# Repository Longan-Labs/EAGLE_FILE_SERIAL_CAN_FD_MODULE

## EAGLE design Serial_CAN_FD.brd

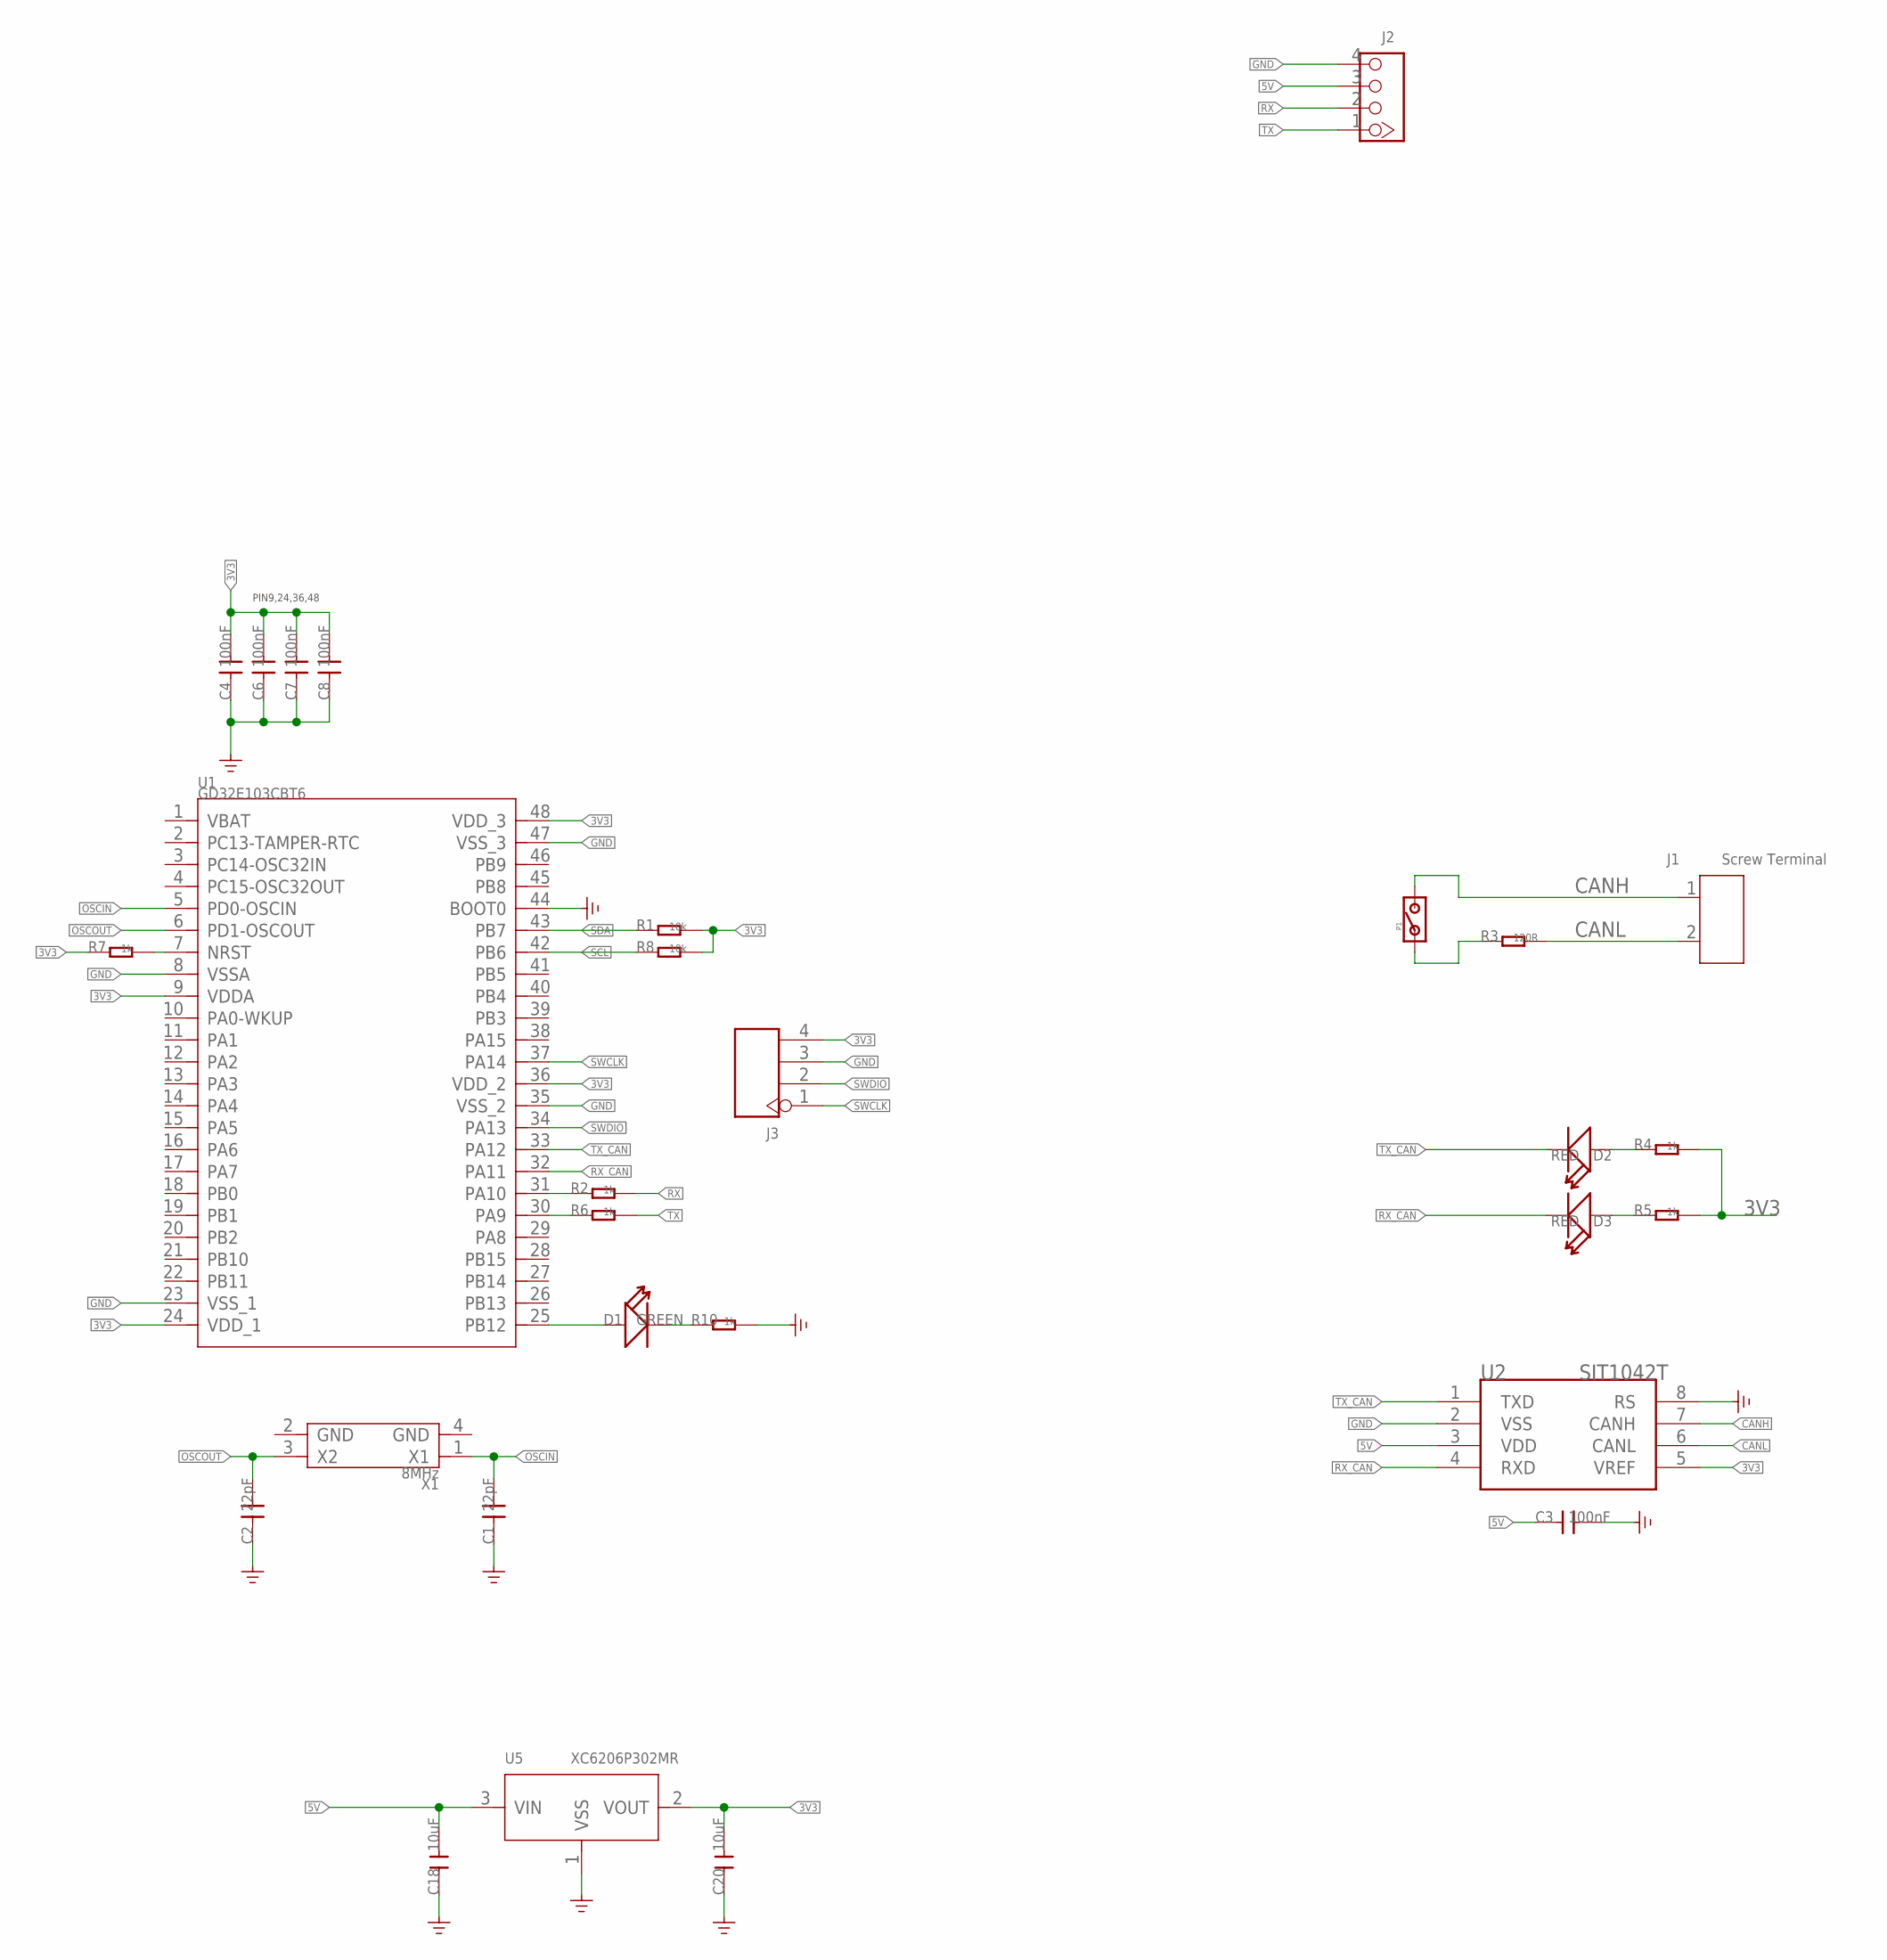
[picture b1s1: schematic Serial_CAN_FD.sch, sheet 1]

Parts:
C1, C2: 22pF; 0603
C3, C4, C6, C7, C8: 100nF; 0603
C18, C20: 10uF; C0603
D1: GREEN; LED-0603
D2, D3: RED; LED-0603
J1: Screw Terminal; 2P-3.5
J2: 320110033; HW4-2.0
J3: HEADER-4P-65/35MIL; H4-2.54
P1: PAD-JUMPER-2P; 2P-SMD-1.78X1.27
R1, R8: 10k; 0603
R2, R4, R5, R6, R7, R10: 1k; 0603
R3: 120R; 0603
U1: GD32E103CBT6; LQFP48
U2: SIT1042T; SOIC8-6.0
U5: XC6206P302MR; SOT-23
X1: 8MHz; X4-SMD-3.2X2.5X0.7MM

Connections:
3V3: C4.2, C6.2, C7.2, C8.2, C20.2, J3.4, R1.2, R4.2, R5.2, R7.1, R8.2, U1.9 (VDDA), U1.24 (VDD_1), U1.36 (VDD_2), U1.48 (VDD_3), U2.5 (VREF), U5.2 (VOUT)
5V: C3.1, C18.2, J2.3, U2.3 (VDD), U5.3 (VIN)
CANH: J1.1, P1.2, U2.7 (CANH)
CANL: J1.2, R3.2, U2.6 (CANL)
GND: C1.1, C2.1, C3.2, C4.1, C6.1, C7.1, C8.1, C18.1, C20.1, J2.4, J3.3, R10.2, U1.8 (VSSA), U1.23 (VSS_1), U1.35 (VSS_2), U1.44 (BOOT0), U1.47 (VSS_3), U2.2 (VSS), U2.8 (RS), U5.1 (VSS)
unnamed: P1.1, R3.1
unnamed: D2.+, R4.1
unnamed: R2.1, U1.31 (PA10)
unnamed: R6.1, U1.30 (PA9)
unnamed: D1.+, U1.25 (PB12)
unnamed: R7.2, U1.7 (NRST)
unnamed: D1.-, R10.1
unnamed: D3.+, R5.1
OSCIN: C1.2, U1.5 (PD0-OSCIN), X1.1 (X1)
OSCOUT: C2.2, U1.6 (PD1-OSCOUT), X1.3 (X2)
RX: J2.2, R2.2
RX_CAN: D3.-, U1.32 (PA11), U2.4 (RXD)
SCL: R8.1, U1.42 (PB6)
SDA: R1.1, U1.43 (PB7)
SWCLK: J3.1, U1.37 (PA14)
SWDIO: J3.2, U1.34 (PA13)
TX: J2.1, R6.2
TX_CAN: D2.-, U1.33 (PA12), U2.1 (TXD)

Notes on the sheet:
PIN9,24,36,48

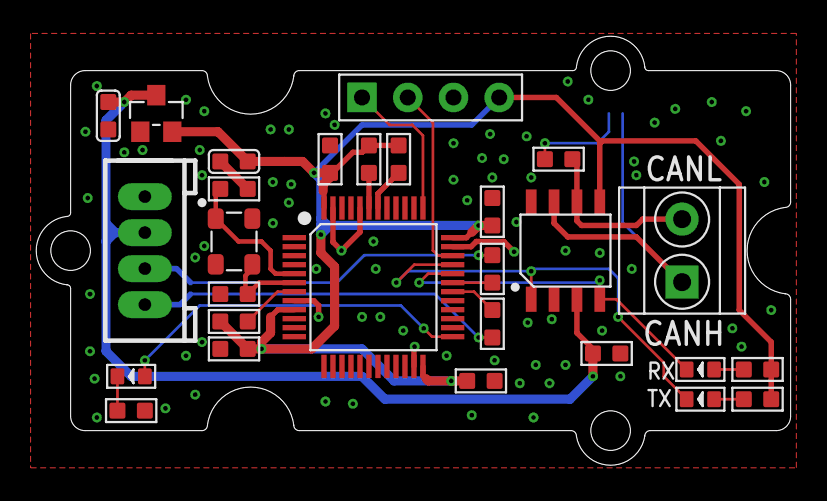
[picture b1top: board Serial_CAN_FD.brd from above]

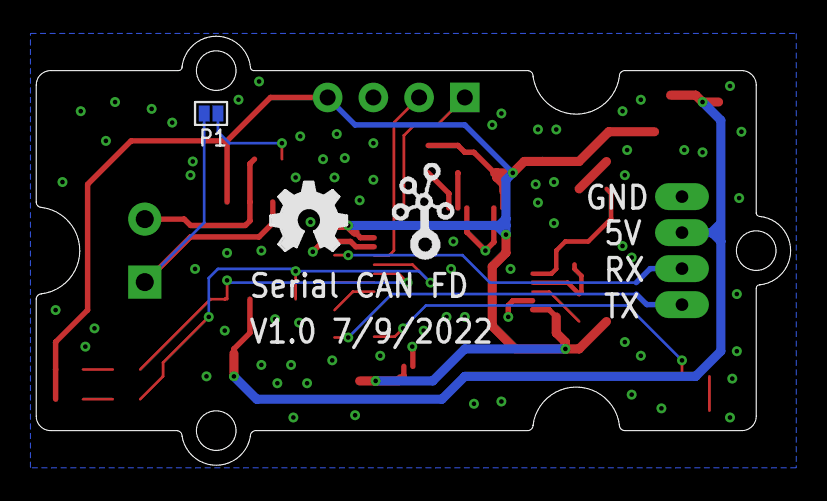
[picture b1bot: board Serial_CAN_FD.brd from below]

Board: 2 copper layers, 41.9 x 23.8 mm, 32 parts (3 on the bottom side), 23 nets.

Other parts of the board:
U3: GROVE-TEST-PLATFORM
U$5: OSHW_FILLX150_NOTEXT
U$9: GROVE-SILK-SMALL
